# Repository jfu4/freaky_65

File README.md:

# freaky_65
This is my first mechanical keybaord PCB.

Specifications:
- 65 % Layout
- USB-C
- STM32MCU
- Rotary encoder
- RGB Lighting
- Custom key mapping
- Modular mounting holes

Avatar Fire Nation Build:  

Japanese Black and White Office Build:

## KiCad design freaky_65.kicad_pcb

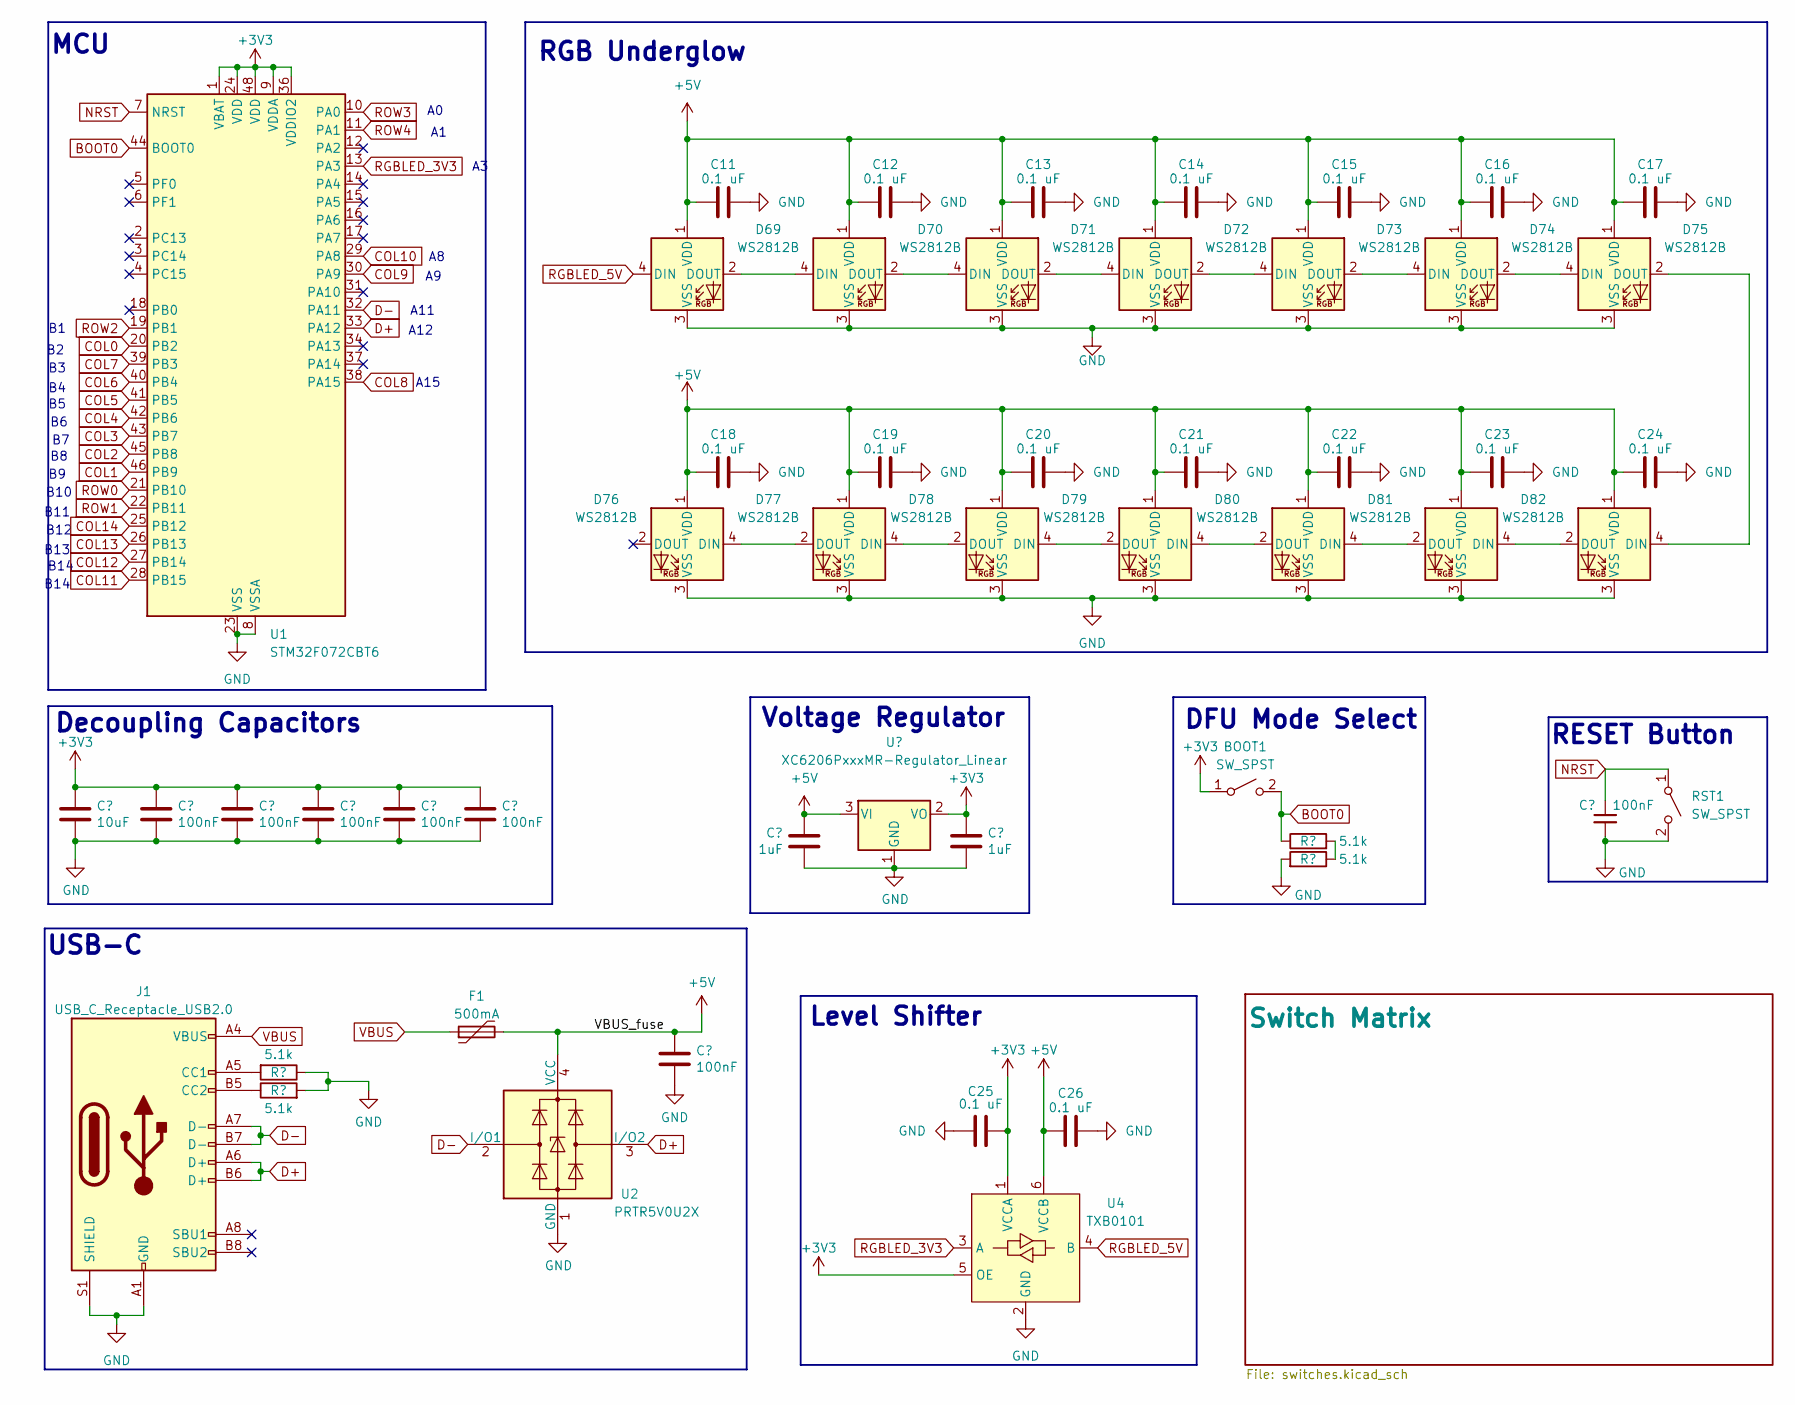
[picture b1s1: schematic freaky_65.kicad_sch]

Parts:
BOOT1: SW_SPST; SW_SPST_TL3342
C1, C3, C4, C5, C6, C7, C8: 100nF; C_0402_1005Metric; LCSC C307331
C2: 10uF; C_0603_1608Metric; LCSC C307331
C9, C10: 1uF; C_0402_1005Metric; LCSC C307331
C11, C12, C13, C14, C15, C16, C17, C18, C19, C20, C21, C22, C23, C24, C25, C26: 0.1 uF; C_0402_1005Metric_Pad0.74x0.62mm_HandSolder
D69, D70, D71, D72, D73, D74, D75, D76, D77, D78, D79, D80, D81, D82: WS2812B; LED_WS2812B_PLCC4_5.0x5.0mm_P3.2mm
F1: 500mA; Fuse_1206_3216Metric; LCSC C135341
J1: USB_C_Receptacle_USB2.0; USB_C_Receptacle_HRO_TYPE-C-31-M-12; JlcRotOffset 180
R1, R2, R3, R4: 5.1k; R_0402_1005Metric
RST1: SW_SPST; SW_SPST_TL3342
U1: STM32F072CBT6; LQFP-48_7x7mm_P0.5mm; JlcRotOffset 90
U2: PRTR5V0U2X; SOT-143; LCSC C2827688
U3: XC6206PxxxMR-Regulator_Linear; SOT-23; LCSC C5446
U4: TXB0101; SOT-363_SC-70-6_Handsoldering; LCSC C324081

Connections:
+3V3: BOOT1.1 (A), C2.1, C3.1, C4.1, C5.1, C6.1, C7.1, C10.1, C25.1, U1.1 (VBAT), U1.9 (VDDA), U1.24 (VDD), U1.36 (VDDIO2), U1.48 (VDD), U3.2 (VO), U4.1 (VCCA), U4.5 (OE); also elsewhere on the board
+5V: C8.1, C9.1, C11.1, C12.1, C13.1, C14.1, C15.1, C16.1, C17.1, C18.1, C19.1, C20.1, C21.1, C22.1, C23.1, C24.1, C26.1, D69.1 (VDD), D70.1 (VDD), D71.1 (VDD), D72.1 (VDD), D73.1 (VDD), D74.1 (VDD), D75.1 (VDD), D76.1 (VDD), D77.1 (VDD), D78.1 (VDD), D79.1 (VDD), D80.1 (VDD), D81.1 (VDD), D82.1 (VDD), F1.2, U2.4 (VCC), U3.3 (VI), U4.6 (VCCB)
BOOT0: BOOT1.2 (B), R3.1, U1.44 (BOOT0)
COL0: U1.20 (PB2); also elsewhere on the board
COL1: U1.46 (PB9); also elsewhere on the board
COL2: U1.45 (PB8); also elsewhere on the board
COL3: U1.43 (PB7); also elsewhere on the board
COL4: U1.42 (PB6); also elsewhere on the board
COL5: U1.41 (PB5); also elsewhere on the board
COL6: U1.40 (PB4); also elsewhere on the board
COL7: U1.39 (PB3); also elsewhere on the board
COL8: U1.38 (PA15); also elsewhere on the board
COL9: U1.30 (PA9); also elsewhere on the board
COL10: U1.29 (PA8); also elsewhere on the board
COL11: U1.28 (PB15); also elsewhere on the board
COL12: U1.27 (PB14); also elsewhere on the board
COL13: U1.26 (PB13); also elsewhere on the board
COL14: U1.25 (PB12); also elsewhere on the board
D+: J1.A6 (D+), J1.B6 (D+), U1.33 (PA12), U2.3 (I/O2)
D-: J1.A7 (D-), J1.B7 (D-), U1.32 (PA11), U2.2 (I/O1)
GND: C1.2, C2.2, C3.2, C4.2, C5.2, C6.2, C7.2, C8.2, C9.2, C10.2, C11.2, C12.2, C13.2, C14.2, C15.2, C16.2, C17.2, C18.2, C19.2, C20.2, C21.2, C22.2, C23.2, C24.2, C25.2, C26.2, D69.3 (VSS), D70.3 (VSS), D71.3 (VSS), D72.3 (VSS), D73.3 (VSS), D74.3 (VSS), D75.3 (VSS), D76.3 (VSS), D77.3 (VSS), D78.3 (VSS), D79.3 (VSS), D80.3 (VSS), D81.3 (VSS), D82.3 (VSS), J1.A1 (GND), J1.A12 (GND), J1.B1 (GND), J1.B12 (GND), J1.S1 (SHIELD), R1.1, R2.2, R4.2, RST1.2 (B), U1.8 (VSSA), U1.23 (VSS), U1.35 (VSS), U1.47 (VSS), U2.1 (GND), U3.1 (GND), U4.2 (GND); also elsewhere on the board
NRST: C1.1, RST1.1 (A), U1.7 (NRST)
unnamed: D69.2 (DOUT), D70.4 (DIN)
unnamed: D70.2 (DOUT), D71.4 (DIN)
unnamed: D71.2 (DOUT), D72.4 (DIN)
unnamed: D72.2 (DOUT), D73.4 (DIN)
unnamed: D73.2 (DOUT), D74.4 (DIN)
unnamed: D74.2 (DOUT), D75.4 (DIN)
unnamed: D75.2 (DOUT), D82.4 (DIN)
unnamed: D76.4 (DIN), D77.2 (DOUT)
unnamed: D77.4 (DIN), D78.2 (DOUT)
unnamed: D78.4 (DIN), D79.2 (DOUT)
unnamed: D79.4 (DIN), D80.2 (DOUT)
unnamed: D80.4 (DIN), D81.2 (DOUT)
unnamed: D81.4 (DIN), D82.2 (DOUT)
unnamed: J1.A5 (CC1), R1.2
unnamed: J1.B5 (CC2), R2.1
unnamed: R3.2, R4.1
RGBLED_3V3: U1.13 (PA3), U4.3 (A)
RGBLED_5V: D69.4 (DIN), U4.4 (B)
ROW0: U1.21 (PB10); also elsewhere on the board
ROW1: U1.22 (PB11); also elsewhere on the board
ROW2: U1.19 (PB1); also elsewhere on the board
ROW3: U1.10 (PA0); also elsewhere on the board
ROW4: U1.11 (PA1); also elsewhere on the board
VBUS: F1.1, J1.A4 (VBUS), J1.A9 (VBUS), J1.B4 (VBUS), J1.B9 (VBUS)

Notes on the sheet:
USB-C
B13
Level Shifter
DFU Mode Select
B12
MCU
RESET Button
B14
A11
A15
A12
B10
B11
RGB Underglow
Decoupling Capacitors
Voltage Regulator

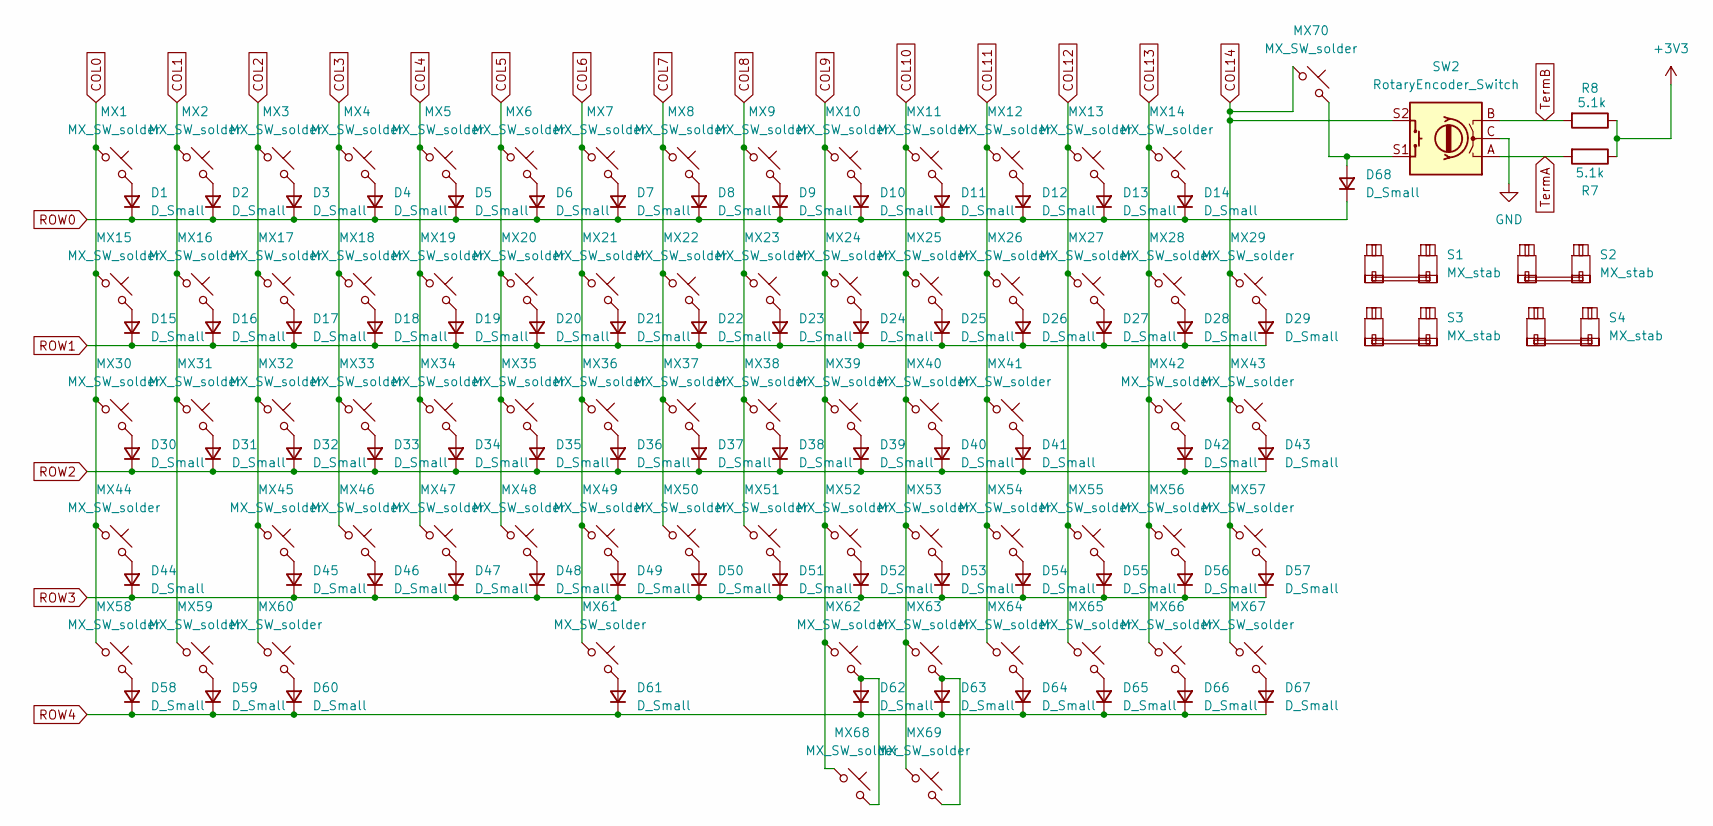
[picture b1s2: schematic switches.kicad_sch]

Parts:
D1, D2, D3, D4, D5, D6, D7, D8, D9, D10, D11, D12, D13, D14, D15, D16, D17, D18, D19, D20, D21, D22, D23, D24, D25, D26, D27, D28, D29, D30, D31, D32, D33, D34, D35, D36, D37, D38, D39, D40, D41, D42, D43, D44, D45, D46, D47, D48, D49, D50, D51, D52, D53, D54, D55, D56, D57, D58, D59, D60, D61, D62, D63, D64, D65, D66, D67, D68: D_Small; D_SOD-123
MX1, MX2, MX3, MX4, MX5, MX6, MX7, MX8, MX9, MX10, MX11, MX12, MX13, MX14, MX16, MX17, MX18, MX19, MX20, MX21, MX22, MX23, MX24, MX25, MX26, MX27, MX29, MX31, MX32, MX33, MX34, MX35, MX36, MX37, MX38, MX39, MX40, MX41, MX42, MX43, MX44, MX45, MX46, MX47, MX48, MX49, MX50, MX51, MX52, MX53, MX54, MX56, MX57, MX61, MX62, MX63, MX64, MX65, MX66, MX67, MX70: MX_SW_solder; SW_MX_1u
MX15, MX28: MX_SW_solder; SW_MX_1.5u
MX30, MX55: MX_SW_solder; SW_MX_1.75u
MX58, MX59, MX60, MX68, MX69: MX_SW_solder; SW_MX_1.25u
R7, R8: 5.1k; R_0603_1608Metric_Pad0.98x0.95mm_HandSolder
S1: MX_stab; STAB_MX_P_6.25u
S2, S3: MX_stab; STAB_MX_2.25u
S4: MX_stab; STAB_MX_2u
SW2: RotaryEncoder_Switch; ROT_Alps_EC11E-Switch

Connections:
+3V3: R7.1, R8.1; also elsewhere on the board
COL0: MX1.1, MX15.1, MX30.1, MX44.1, MX58.1; also elsewhere on the board
COL1: MX2.1, MX16.1, MX31.1, MX59.1; also elsewhere on the board
COL2: MX3.1, MX17.1, MX32.1, MX45.1, MX60.1; also elsewhere on the board
COL3: MX4.1, MX18.1, MX33.1, MX46.1; also elsewhere on the board
COL4: MX5.1, MX19.1, MX34.1, MX47.1; also elsewhere on the board
COL5: MX6.1, MX20.1, MX35.1, MX48.1; also elsewhere on the board
COL6: MX7.1, MX21.1, MX36.1, MX49.1, MX61.1; also elsewhere on the board
COL7: MX8.1, MX22.1, MX37.1, MX50.1; also elsewhere on the board
COL8: MX9.1, MX23.1, MX38.1, MX51.1; also elsewhere on the board
COL9: MX10.1, MX24.1, MX39.1, MX52.1, MX62.1, MX68.1; also elsewhere on the board
COL10: MX11.1, MX25.1, MX40.1, MX53.1, MX63.1, MX69.1; also elsewhere on the board
COL11: MX12.1, MX26.1, MX41.1, MX54.1, MX64.1; also elsewhere on the board
COL12: MX13.1, MX27.1, MX55.1, MX65.1; also elsewhere on the board
COL13: MX14.1, MX28.1, MX42.1, MX56.1, MX66.1; also elsewhere on the board
COL14: MX29.1, MX43.1, MX57.1, MX67.1, MX70.1, SW2.S2; also elsewhere on the board
GND: SW2.C; also elsewhere on the board
unnamed: D1.2 (A), MX1.2
unnamed: D2.2 (A), MX2.2
unnamed: D3.2 (A), MX3.2
unnamed: D4.2 (A), MX4.2
unnamed: D5.2 (A), MX5.2
unnamed: D6.2 (A), MX6.2
unnamed: D7.2 (A), MX7.2
unnamed: D8.2 (A), MX8.2
unnamed: D9.2 (A), MX9.2
unnamed: D10.2 (A), MX10.2
unnamed: D11.2 (A), MX11.2
unnamed: D12.2 (A), MX12.2
unnamed: D13.2 (A), MX13.2
unnamed: D14.2 (A), MX14.2
unnamed: D15.2 (A), MX15.2
unnamed: D16.2 (A), MX16.2
unnamed: D17.2 (A), MX17.2
unnamed: D18.2 (A), MX18.2
unnamed: D19.2 (A), MX19.2
unnamed: D20.2 (A), MX20.2
unnamed: D21.2 (A), MX21.2
unnamed: D22.2 (A), MX22.2
unnamed: D23.2 (A), MX23.2
unnamed: D24.2 (A), MX24.2
unnamed: D25.2 (A), MX25.2
unnamed: D26.2 (A), MX26.2
unnamed: D27.2 (A), MX27.2
unnamed: D28.2 (A), MX28.2
unnamed: D29.2 (A), MX29.2
unnamed: D30.2 (A), MX30.2
unnamed: D31.2 (A), MX31.2
unnamed: D32.2 (A), MX32.2
unnamed: D33.2 (A), MX33.2
unnamed: D34.2 (A), MX34.2
unnamed: D35.2 (A), MX35.2
unnamed: D36.2 (A), MX36.2
unnamed: D37.2 (A), MX37.2
unnamed: D38.2 (A), MX38.2
unnamed: D39.2 (A), MX39.2
unnamed: D40.2 (A), MX40.2
unnamed: D41.2 (A), MX41.2
unnamed: D42.2 (A), MX42.2
unnamed: D43.2 (A), MX43.2
unnamed: D44.2 (A), MX44.2
unnamed: D45.2 (A), MX45.2
unnamed: D46.2 (A), MX46.2
unnamed: D47.2 (A), MX47.2
unnamed: D48.2 (A), MX48.2
unnamed: D49.2 (A), MX49.2
unnamed: D50.2 (A), MX50.2
unnamed: D51.2 (A), MX51.2
unnamed: D52.2 (A), MX52.2
unnamed: D53.2 (A), MX53.2
unnamed: D54.2 (A), MX54.2
unnamed: D55.2 (A), MX55.2
unnamed: D56.2 (A), MX56.2
unnamed: D57.2 (A), MX57.2
unnamed: D58.2 (A), MX58.2
unnamed: D59.2 (A), MX59.2
unnamed: D60.2 (A), MX60.2
unnamed: D61.2 (A), MX61.2
unnamed: D62.2 (A), MX62.2, MX68.2
unnamed: D63.2 (A), MX63.2, MX69.2
unnamed: D64.2 (A), MX64.2
unnamed: D65.2 (A), MX65.2
unnamed: D66.2 (A), MX66.2
unnamed: D67.2 (A), MX67.2
unnamed: D68.2 (A), MX70.2, SW2.S1
ROW0: D1.1 (K), D2.1 (K), D3.1 (K), D4.1 (K), D5.1 (K), D6.1 (K), D7.1 (K), D8.1 (K), D9.1 (K), D10.1 (K), D11.1 (K), D12.1 (K), D13.1 (K), D14.1 (K), D68.1 (K); also elsewhere on the board
ROW1: D15.1 (K), D16.1 (K), D17.1 (K), D18.1 (K), D19.1 (K), D20.1 (K), D21.1 (K), D22.1 (K), D23.1 (K), D24.1 (K), D25.1 (K), D26.1 (K), D27.1 (K), D28.1 (K), D29.1 (K); also elsewhere on the board
ROW2: D30.1 (K), D31.1 (K), D32.1 (K), D33.1 (K), D34.1 (K), D35.1 (K), D36.1 (K), D37.1 (K), D38.1 (K), D39.1 (K), D40.1 (K), D41.1 (K), D42.1 (K), D43.1 (K); also elsewhere on the board
ROW3: D44.1 (K), D45.1 (K), D46.1 (K), D47.1 (K), D48.1 (K), D49.1 (K), D50.1 (K), D51.1 (K), D52.1 (K), D53.1 (K), D54.1 (K), D55.1 (K), D56.1 (K), D57.1 (K); also elsewhere on the board
ROW4: D58.1 (K), D59.1 (K), D60.1 (K), D61.1 (K), D62.1 (K), D63.1 (K), D64.1 (K), D65.1 (K), D66.1 (K), D67.1 (K); also elsewhere on the board
TermA: R7.2, SW2.A
TermB: R8.2, SW2.B

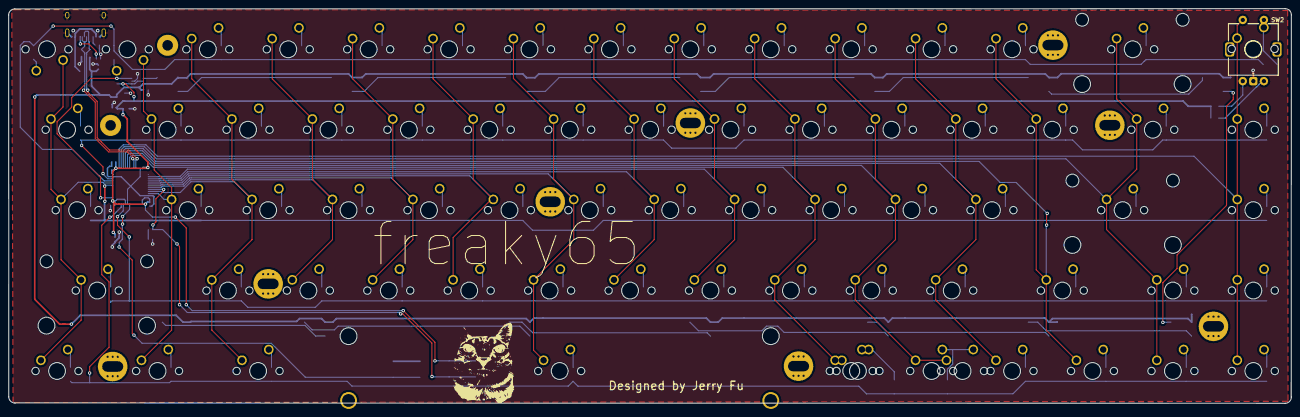
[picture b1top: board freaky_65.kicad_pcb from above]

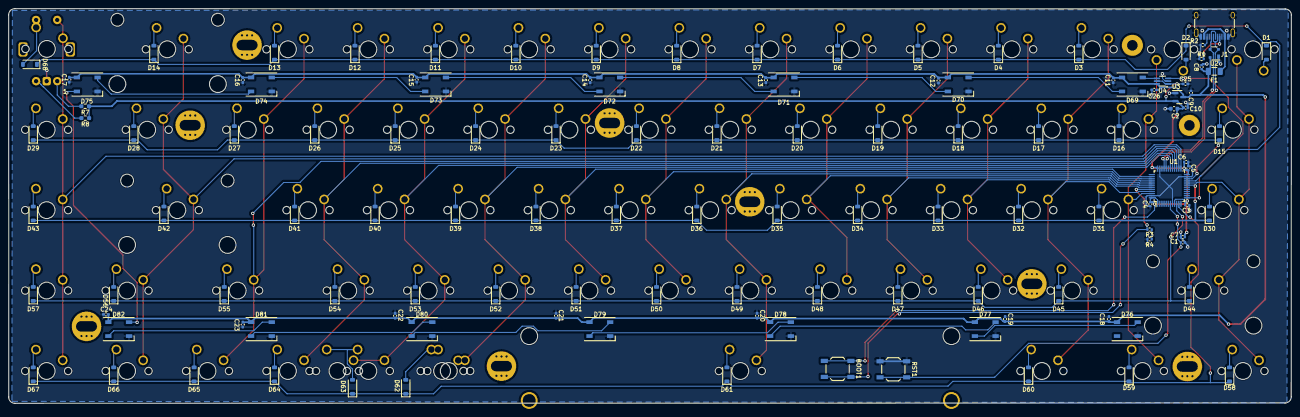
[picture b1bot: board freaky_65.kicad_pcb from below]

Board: 2 copper layers, 303.8 x 93.5 mm, 197 parts (122 on the bottom side), 116 nets.

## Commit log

2025-11-01 Initial commit of existing KiCad project
2025-11-02 Initial commit (reset repo)
2025-11-02 Update images in README.md for builds
    Removed an image of the Japanese Black and White Office Build and added a new image for the same build.
2025-11-02 Fix image tag for Japanese Black and White Office Build
